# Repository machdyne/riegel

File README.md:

# Riegel Computer

Riegel is an FPGA computer designed by Lone Dynamics Corporation.

This repo contains schematics, PCB layouts, pinouts, a 3D-printable case, example gateware and documentation.

Find more information on the [Riegel product page](https://machdyne.com/product/riegel-computer/).

## Blinky 

Building the blinky example requires [Yosys](https://github.com/YosysHQ/yosys), [nextpnr-ice40](https://github.com/YosysHQ/nextpnr) and [IceStorm](https://github.com/YosysHQ/icestorm).

Assuming they are installed, you can simply type `make` to build the gateware, which will be written to output/blinky.bin. You can then use [ldprog](https://github.com/machdyne/ldprog) to write the gateware to the device.

## Zucker

[Zucker](https://github.com/machdyne/zucker) is a RISC-V SOC designed specifically for Riegel hardware.

## USB Bootloader

Riegel supports updating the flash MMOD over its USB-C port with the USB DFU (Device Firmware Upgrade) protocol. When Riegel powers on (or restarts) the USB bootloader waits 5 seconds for a USB command and then continues the boot process, if it receives a command it will wait until the device is detached (with `dfu-util -e`) or rebooted (with `ldprog -r`).

In order to install the USB bootloader you will need to use the ISP header and [ldprog](https://github.com/machdyne/ldprog). Make sure you have first installed the software required to build the Blinky example above.

```
git clone https://github.com/machdyne/tinydfu-bootloader
cd tinydfu-bootloader/boards/riegel
make
make prog
```

Now you can program the flash MMOD over USB:

```
ldprog -r
sudo dfu-util -a 0 -D zucker/output/soc.bin
sudo dfu-util -a 1 -D zucker/apps/lix/lix.bin
```

Note: It may be necessary to remove the MicroSD card before programming with DFU.

Exit the bootloader and continue booting:

```
sudo dfu-util -e -a 0
```

## ISP Header

The ISP header can be used to program the FPGA SRAM as well as the MMOD flash memory. 

```
1 2
3 4
5 6
7 8
```

| Pin | Signal |
| --- | ------ |
| 1 | CSPI\_SS |
| 2 | CSPI\_SCK |
| 3 | CSPI\_SI |
| 4 | CSPI\_SO |
| 5 | CRESET |
| 6 | CDONE |
| 7 | GND |
| 8 | PWR3V3 (out) |

## Board Revisions

| Revision | Notes |
| -------- | ----- |
| V3B | Latest production board |
| V4 | Work in progress; improves USB routing  |

## License

The contents of this repo are released under the [Lone Dynamics Open License](LICENSE.md) with the following exceptions:

- The KiCad design files contain parts of the [kicad-pmod](https://github.com/mithro/kicad-pmod) library which is released under the [Apache License, Version 2.0](https://www.apache.org/licenses/LICENSE-2.0.html).

- The KiCad design files may contain symbols and footprints released under other licenses; please contact us if we've failed to give proper attribution.

Note: You can use these designs for commercial purposes but we ask that instead of producing exact clones, that you either replace our trademarks and logos with your own or add your own next to ours.

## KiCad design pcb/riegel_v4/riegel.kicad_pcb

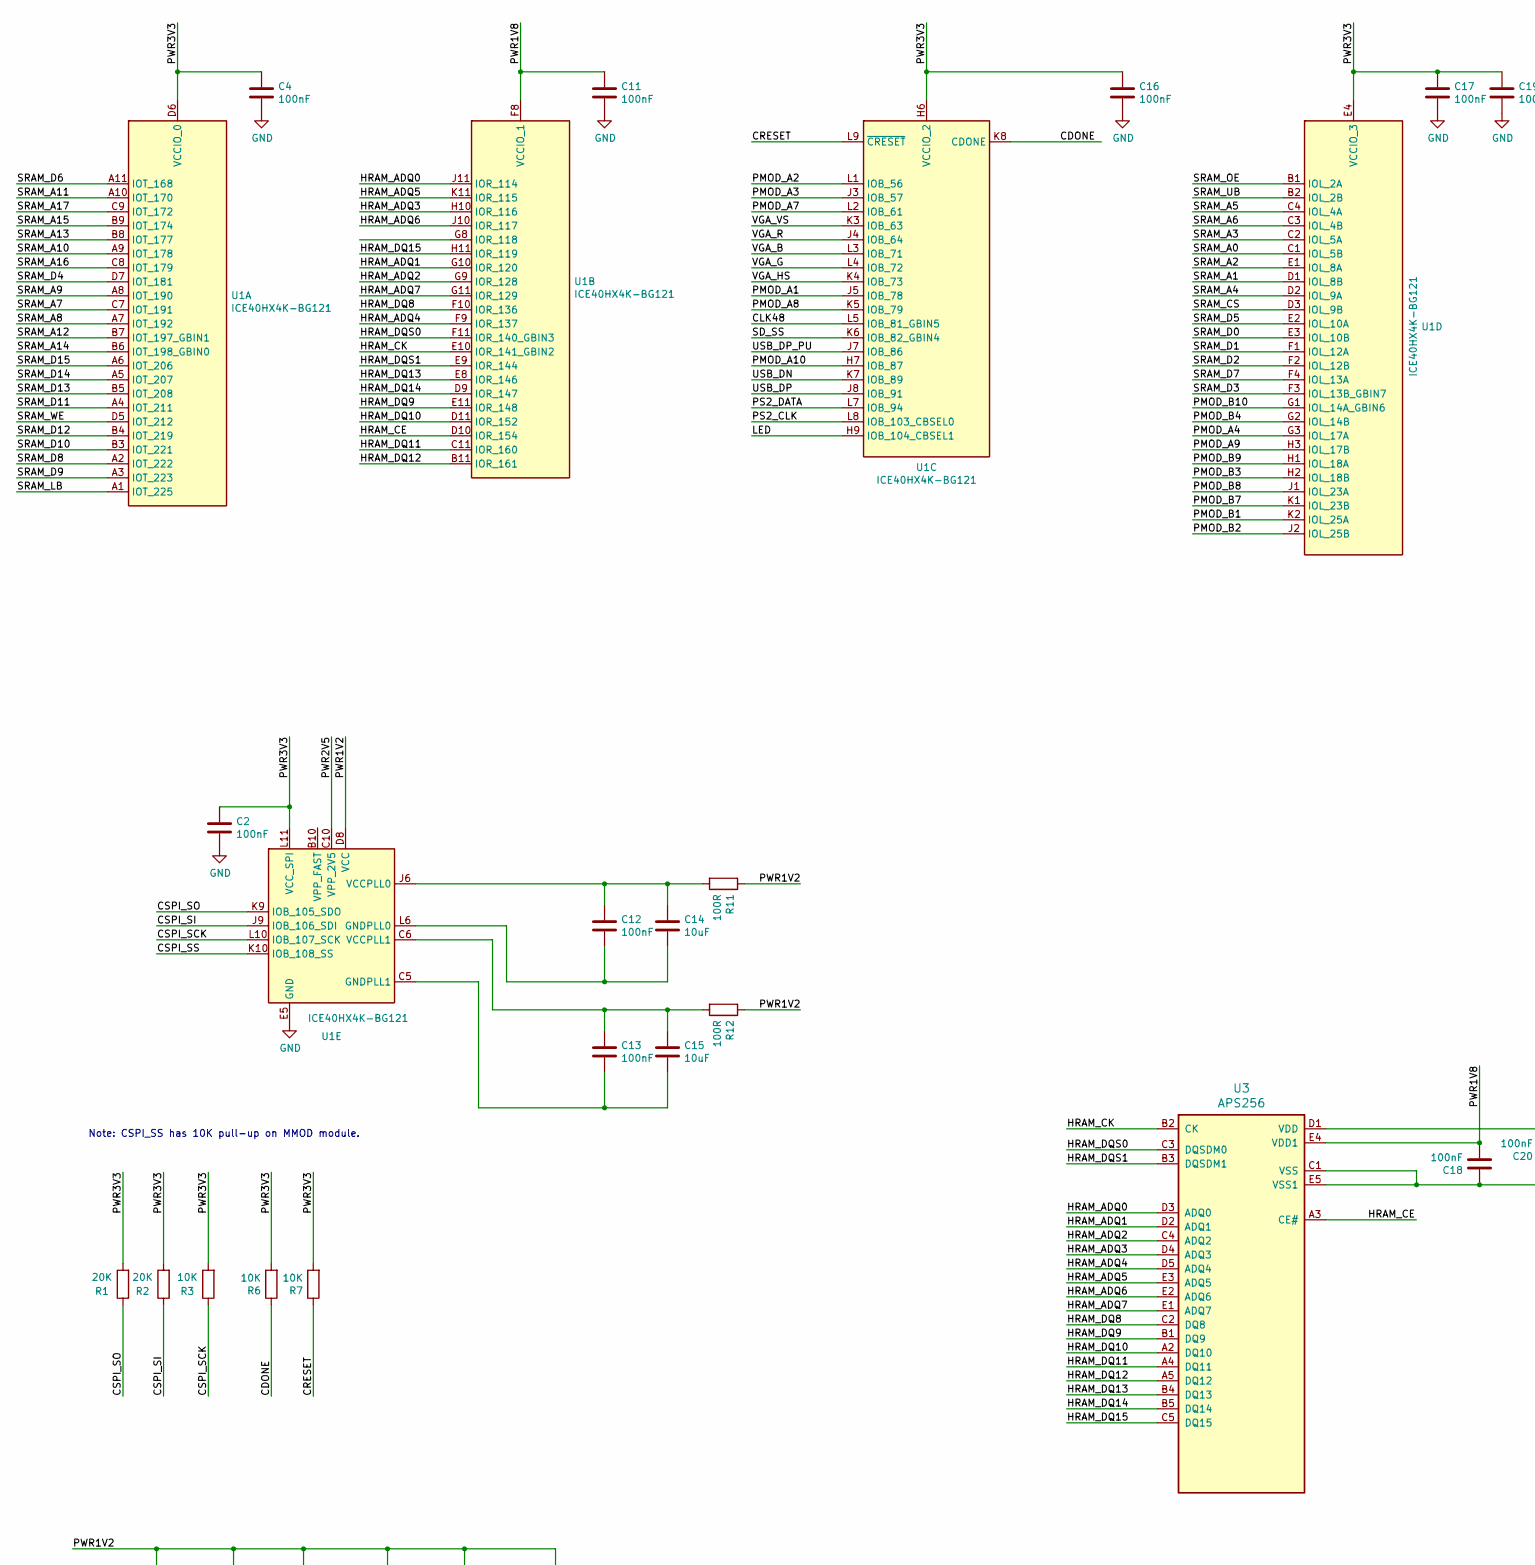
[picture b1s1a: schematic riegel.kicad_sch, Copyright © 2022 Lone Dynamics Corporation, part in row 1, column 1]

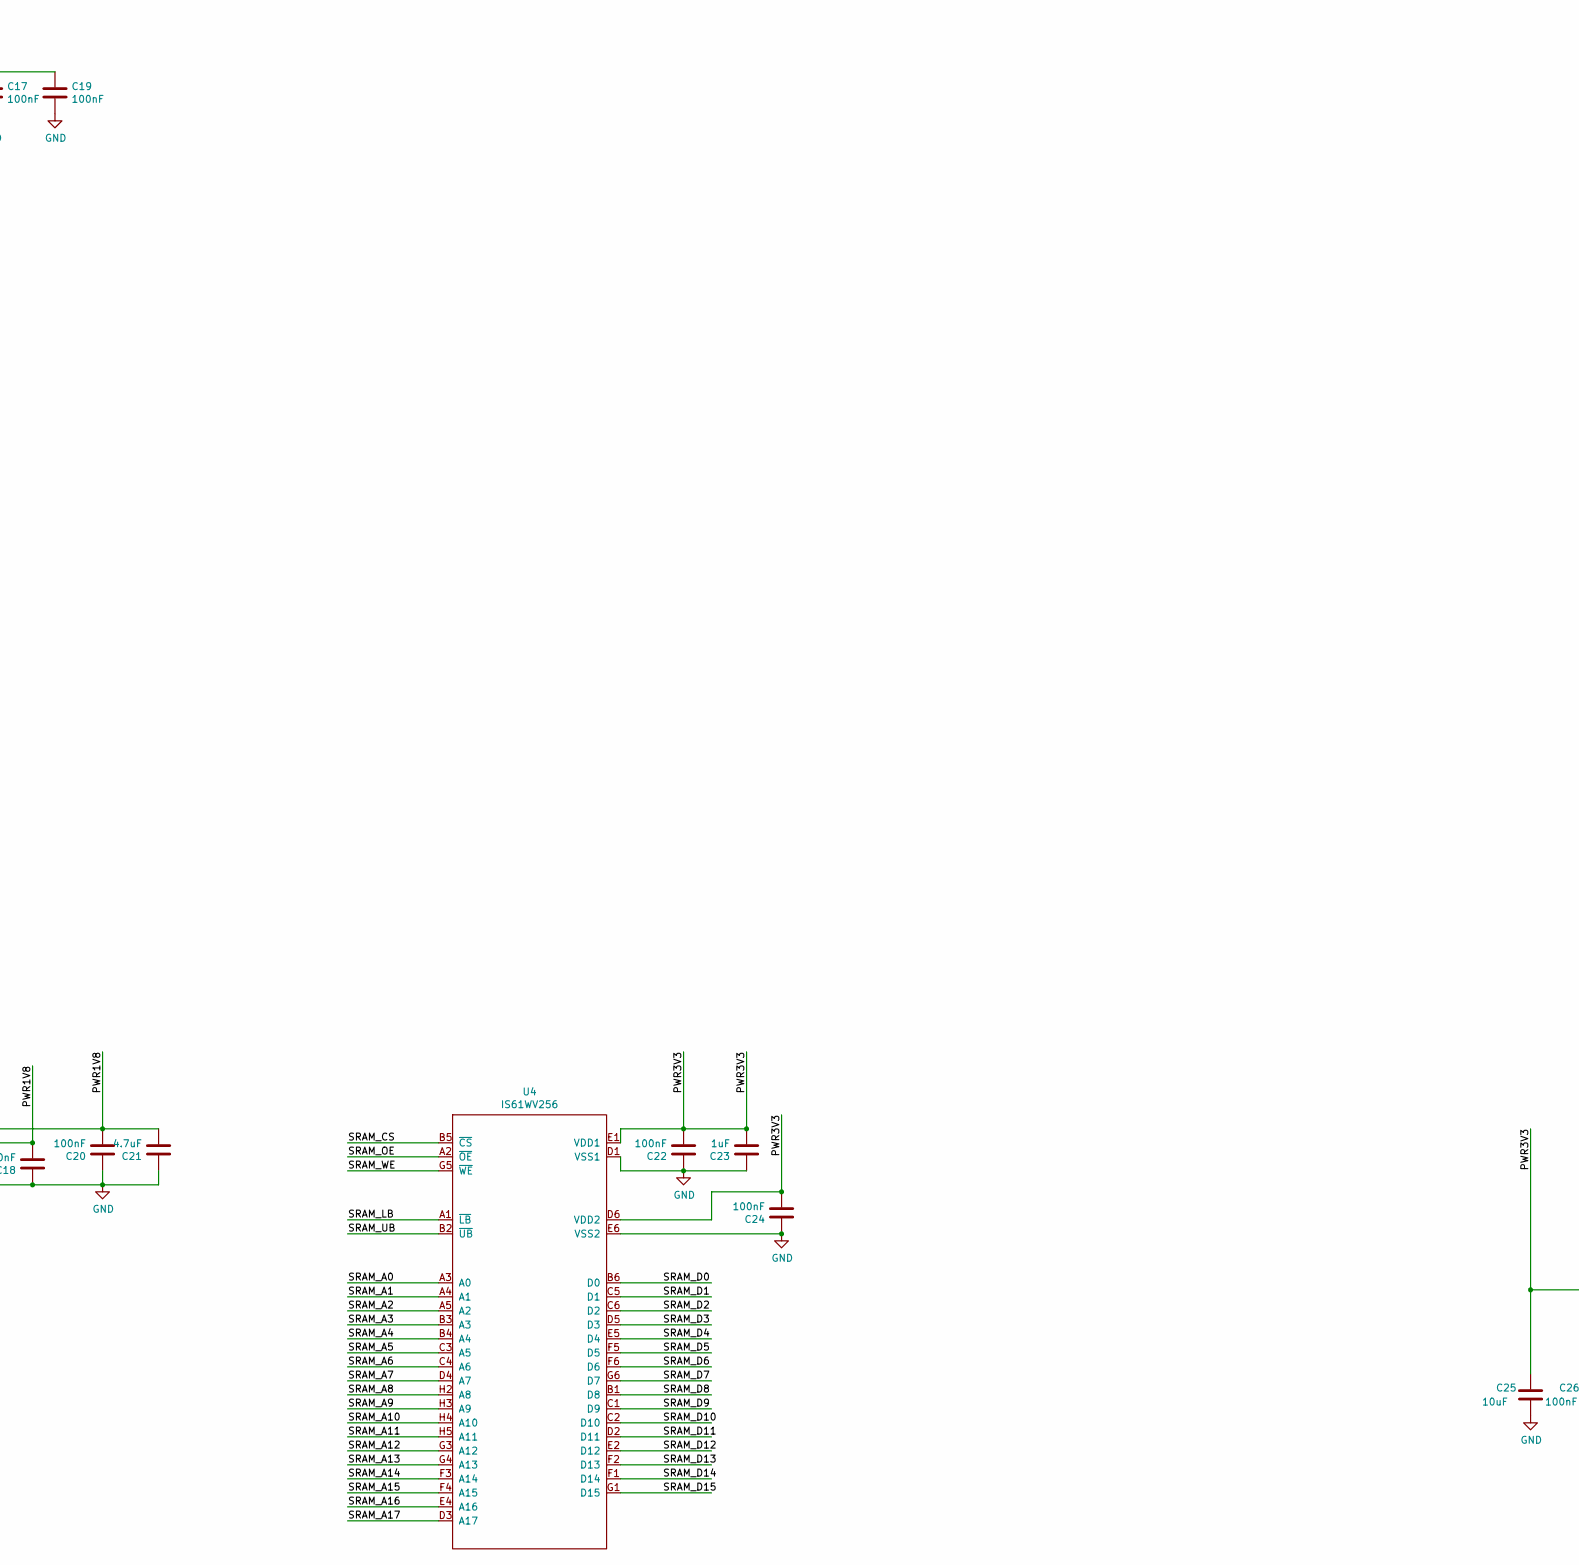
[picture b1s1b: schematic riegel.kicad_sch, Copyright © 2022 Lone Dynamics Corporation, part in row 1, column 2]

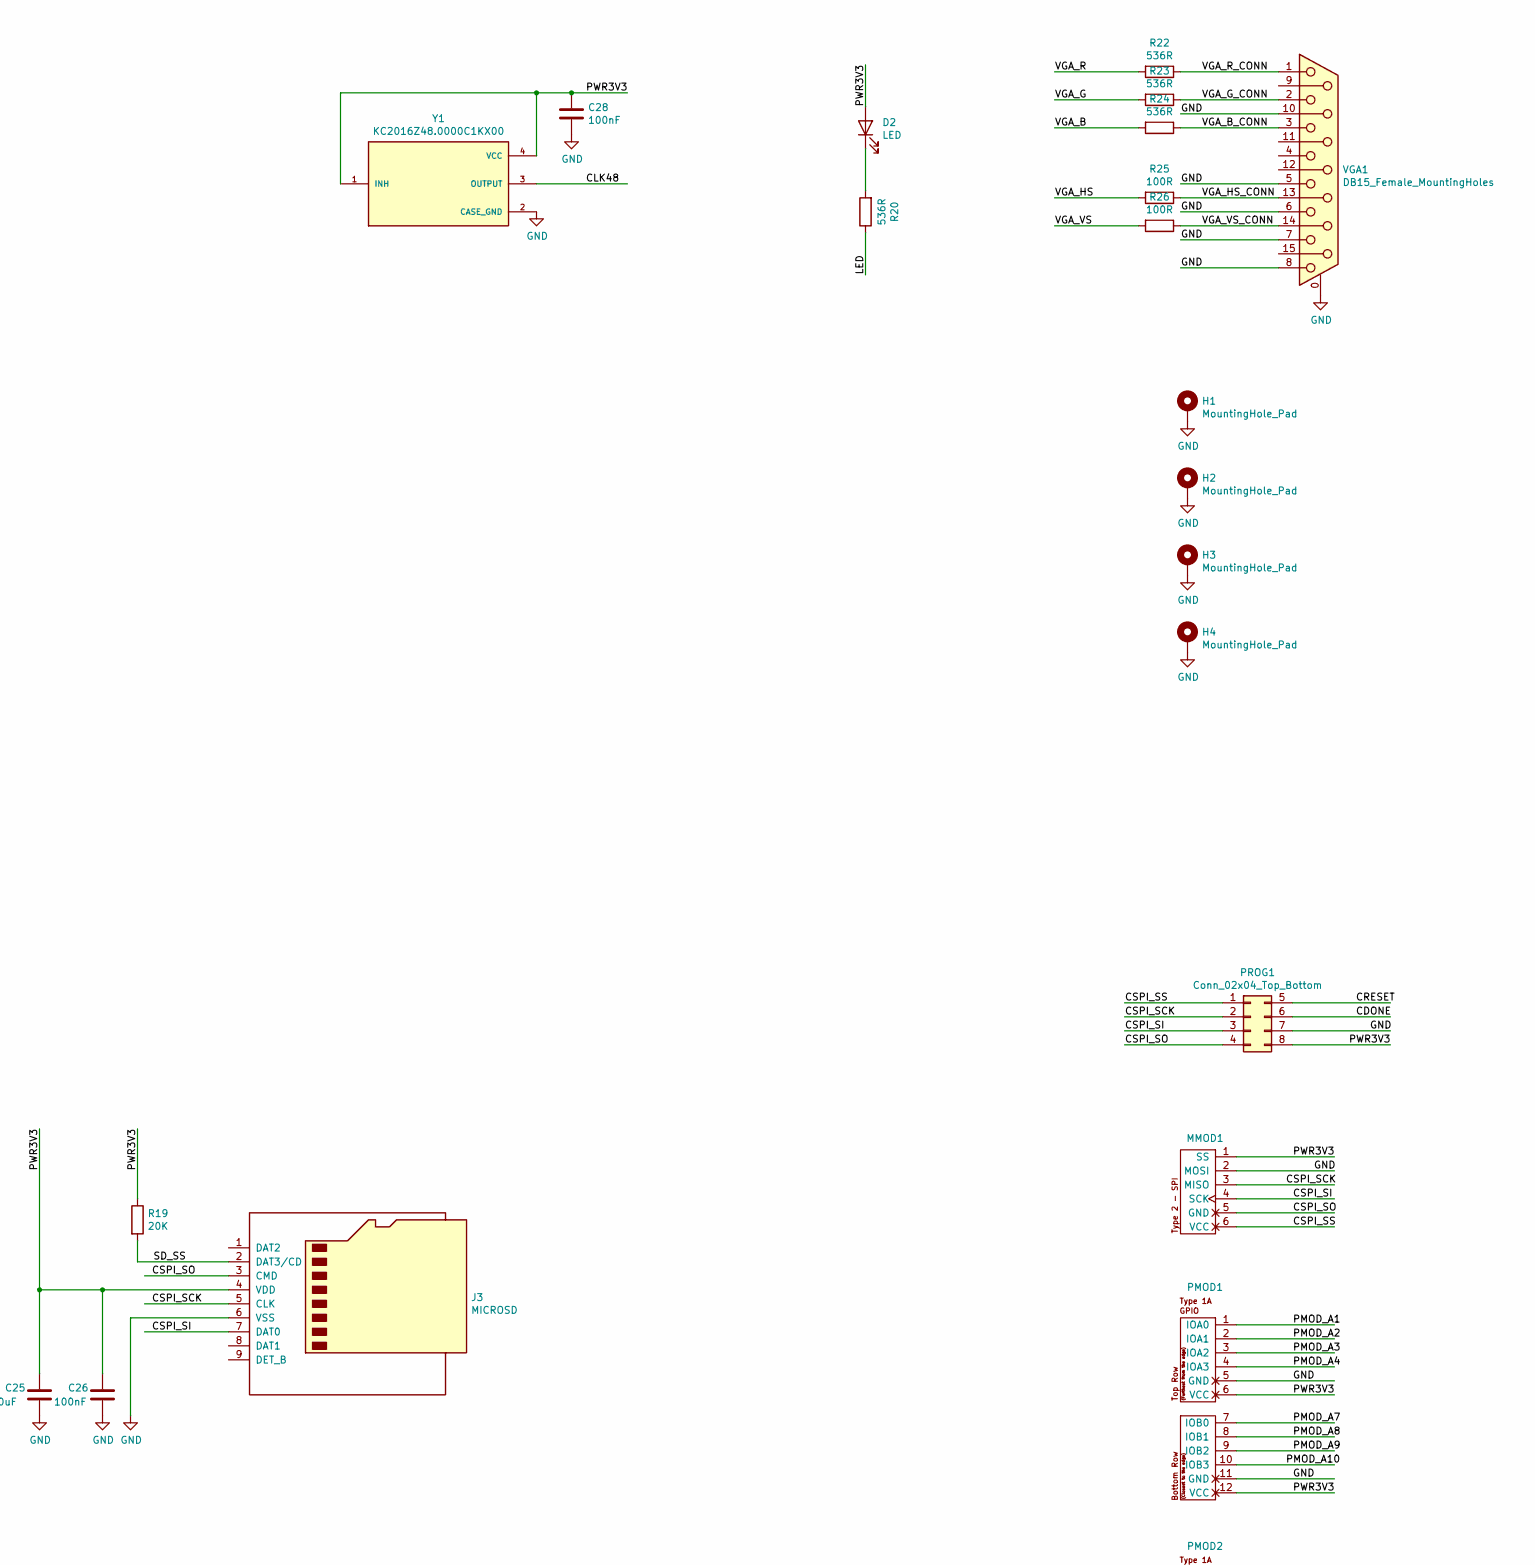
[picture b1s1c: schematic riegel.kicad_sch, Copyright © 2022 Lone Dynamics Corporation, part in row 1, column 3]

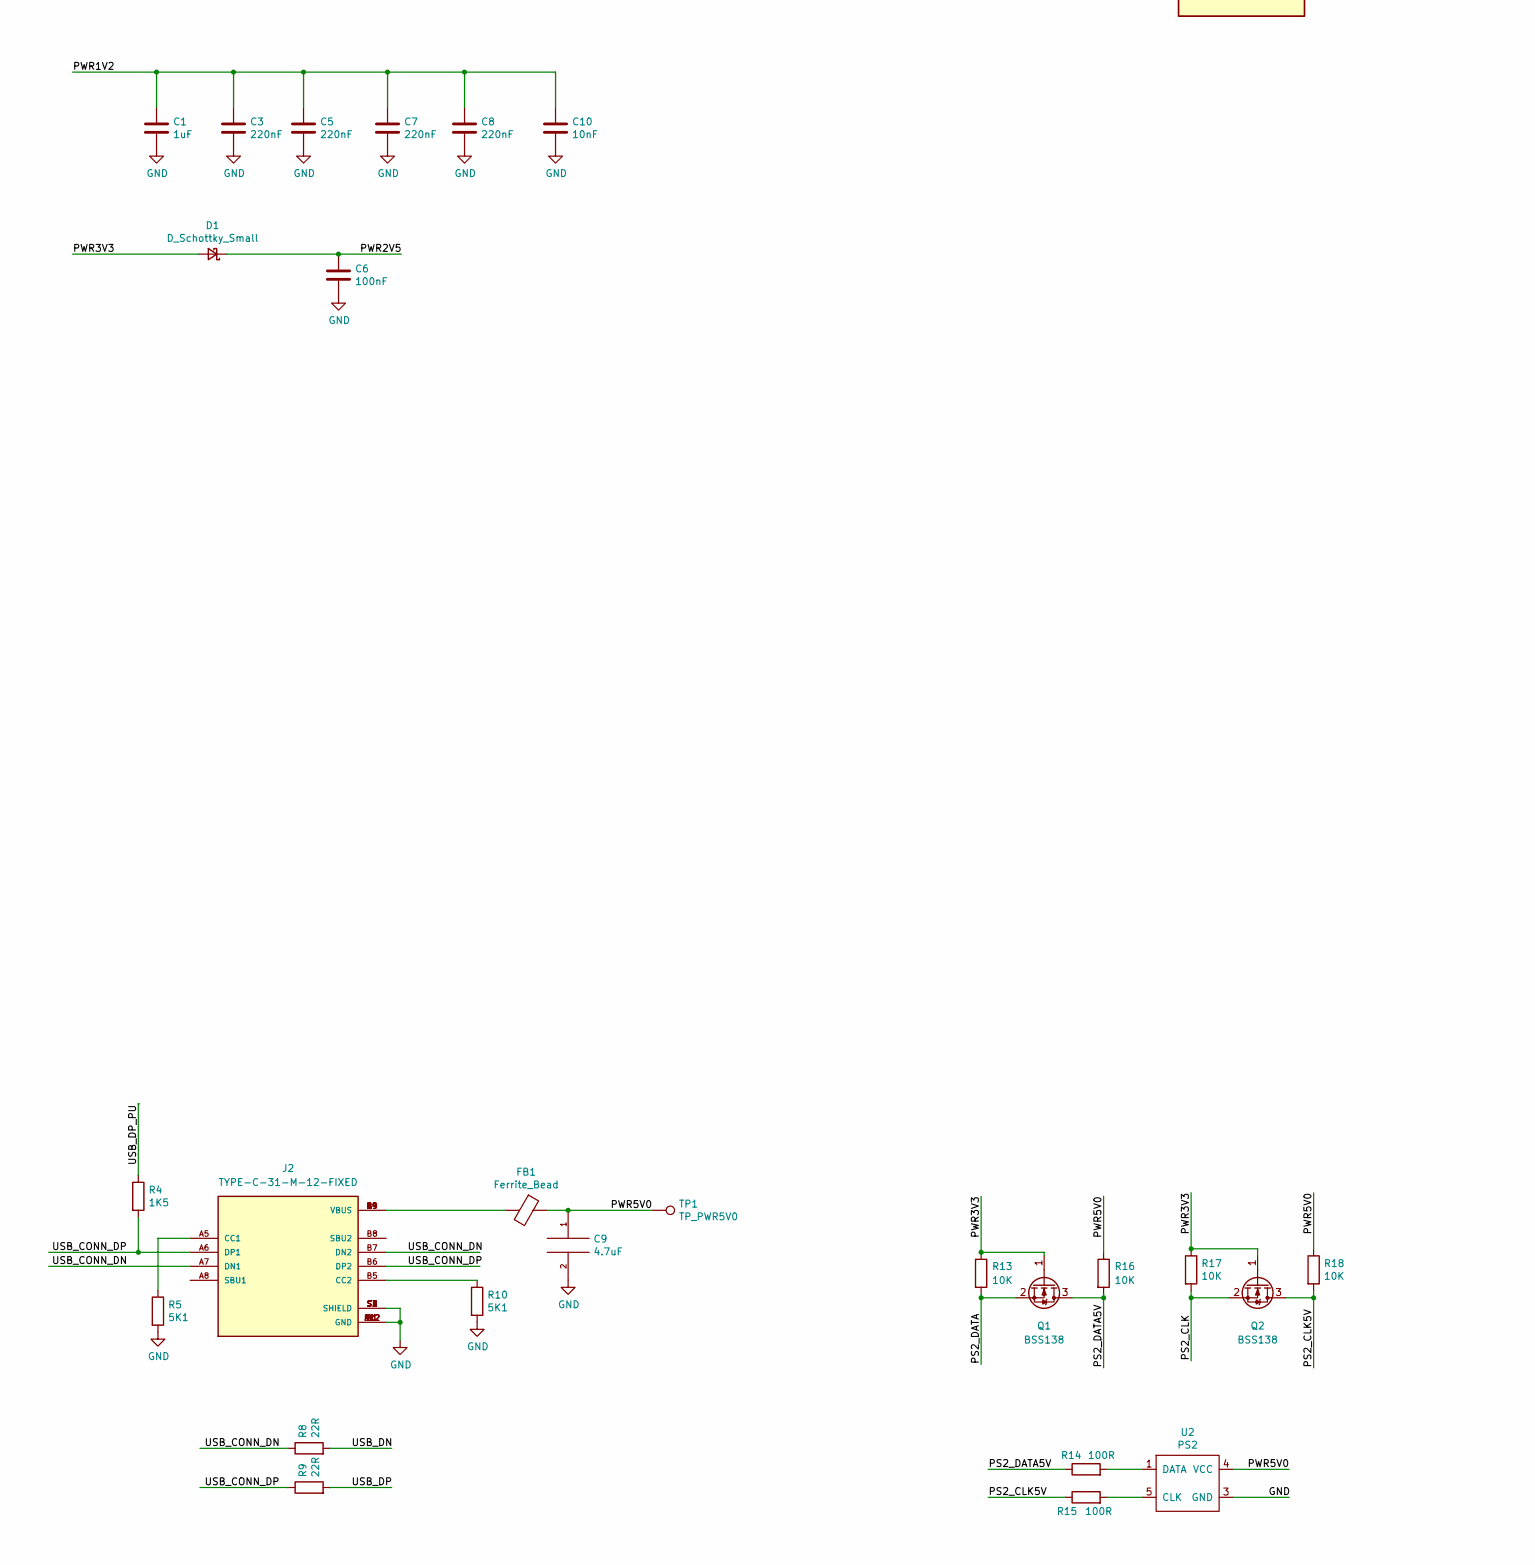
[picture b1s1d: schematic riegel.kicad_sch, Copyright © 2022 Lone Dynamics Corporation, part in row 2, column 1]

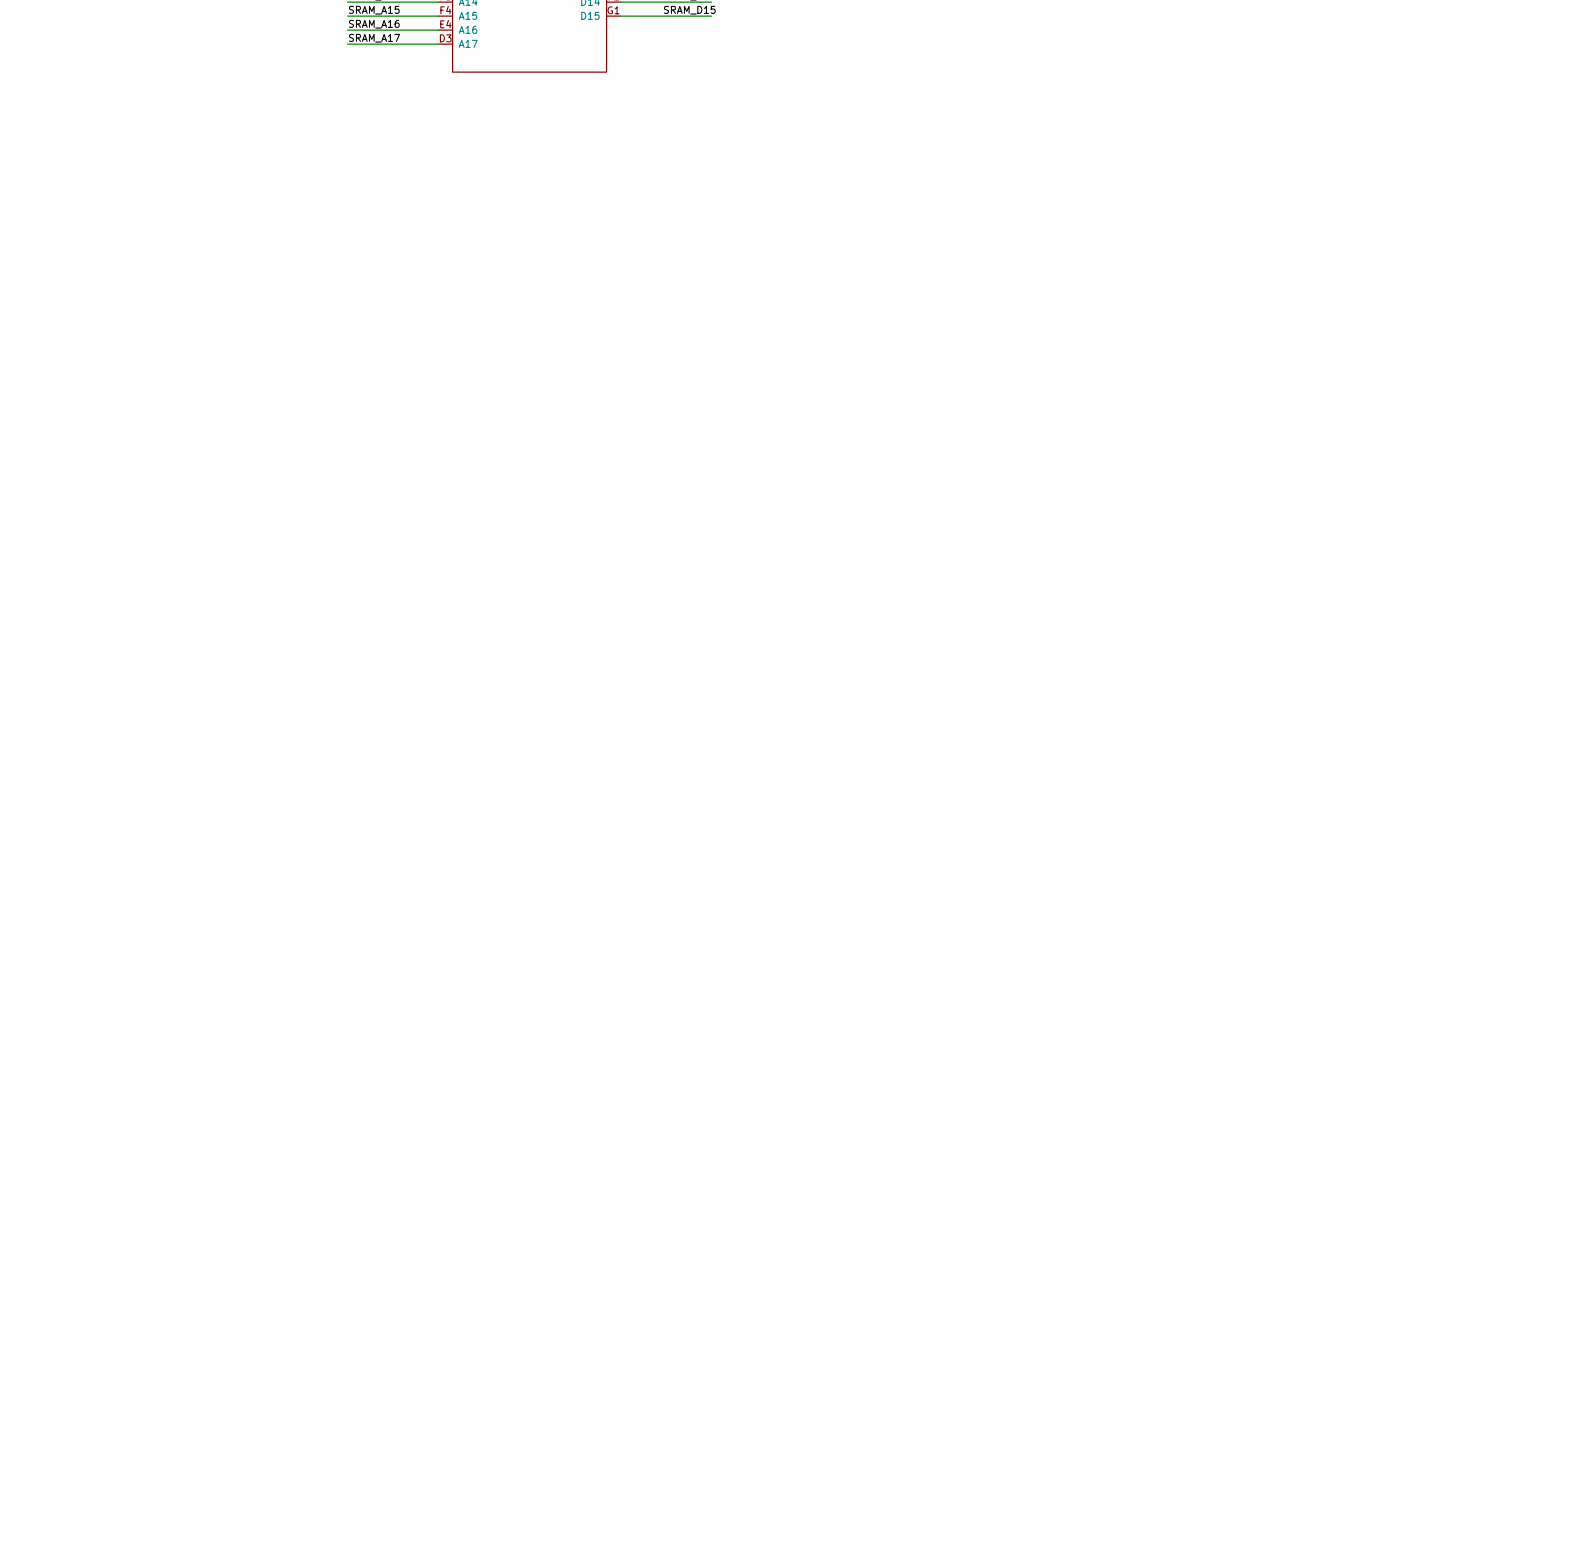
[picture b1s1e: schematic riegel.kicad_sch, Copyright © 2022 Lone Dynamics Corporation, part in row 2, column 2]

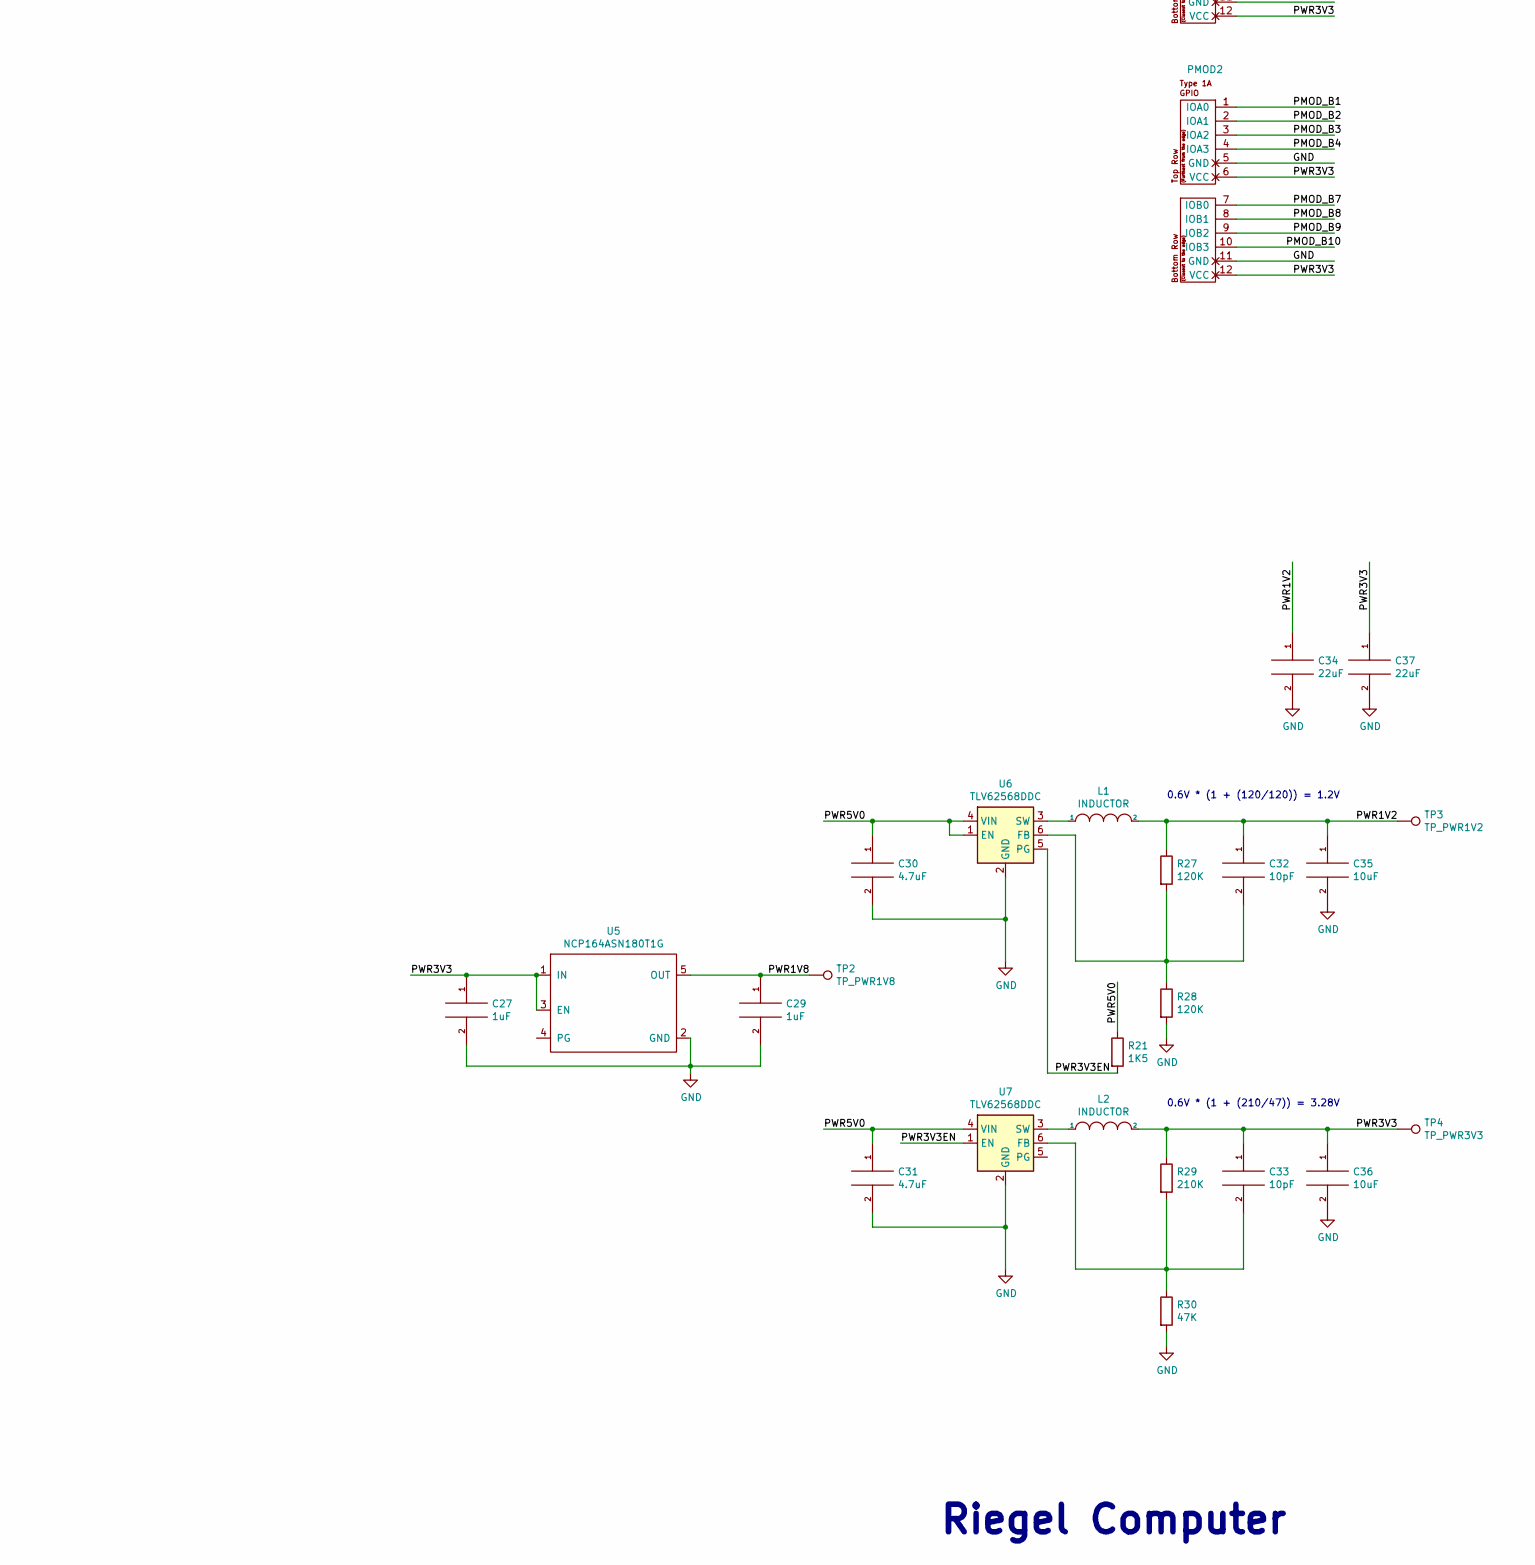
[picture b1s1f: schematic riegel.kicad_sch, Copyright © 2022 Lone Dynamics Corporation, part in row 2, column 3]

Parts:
C1, C27, C29: 1uF; C_0603_1608Metric
C2, C4, C6, C11, C12, C13, C16, C17, C19: 100nF; C_0603_1608Metric
C3, C5, C7, C8: 220nF; C_0603_1608Metric
C9, C21: 4.7uF; R_0603_1608Metric
C10: 10nF; C_0603_1608Metric
C14, C15, C35, C36: 10uF; C_0603_1608Metric
C18, C20, C22, C24, C26, C28: 100nF; R_0603_1608Metric
C23: 1uF; R_0603_1608Metric
C25: 10uF; R_0603_1608Metric
C30, C31: 4.7uF; C_0603_1608Metric
C32, C33: 10pF; C_0603_1608Metric
C34, C37: 22uF; C_0603_1608Metric
D1: D_Schottky_Small; D_0603_1608Metric
D2: LED; LED_0603_1608Metric
FB1: Ferrite_Bead; R_0603_1608Metric
H1, H2, H3, H4: MountingHole_Pad; MountingHole_3.2mm_M3_Pad
J2: TYPE-C-31-M-12-FIXED; USB_C_Receptacle_HRO_TYPE-C-31-M-12; PARTREV A
J3: MICROSD; SDCARD
L1, L2: INDUCTOR; L_0805_2012Metric
MMOD1: PMOD-Device-x1-Type-2-SPI; PinSocket_1x06_P2.54mm_Horizontal
PMOD1, PMOD2: PMOD-Device-x2-Type-1A-GPIO; PMOD_2x06_HOST
PROG1: Conn_02x04_Top_Bottom; PinHeader_2x04_P2.54mm_Vertical
Q1, Q2: BSS138; SOT-323_SC-70
R1, R2, R19: 20K; R_0603_1608Metric
R3, R6, R7, R13, R16, R17, R18: 10K; R_0603_1608Metric
R4, R21: 1K5; R_0603_1608Metric
R5, R10: 5K1; R_0603_1608Metric
R8, R9: 22R; R_0603_1608Metric
R11, R12, R14, R15, R25, R26: 100R; R_0603_1608Metric
R20, R22, R23, R24: 536R; R_0603_1608Metric
R27, R28: 120K; R_0603_1608Metric
R29: 210K; R_0603_1608Metric
R30: 47K; R_0603_1608Metric
TP1: TP_PWR5V0; TestPoint_THTPad_D1.0mm_Drill0.5mm
TP2: TP_PWR1V8; TestPoint_THTPad_D1.0mm_Drill0.5mm
TP3: TP_PWR1V2; TestPoint_THTPad_D1.0mm_Drill0.5mm
TP4: TP_PWR3V3; TestPoint_THTPad_D1.0mm_Drill0.5mm
U1: ICE40HX4K-BG121; BGA-121_9.0x9.0mm_Layout11x11_P0.8mm_Ball0.4mm_Pad0.35mm_NS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
U2: PS2; MINI-DIN-6-FULL-SHIELD
U3: APS256; APS256_BGA_24
U4: IS61WV256; BGA48C75P8X6_800X600X120N
U5: NCP164ASN180T1G; TSOP-5_1.65x3.05mm_P0.95mm
U6, U7: TLV62568DDC; SOT-23-6
VGA1: DB15_Female_MountingHoles; DSUB-15-HD_Female_Horizontal_P2.29x1.98mm_EdgePinOffset3.03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
Y1: KC2016Z48.0000C1KX00; OSC_KC2016Z13.5600C1KX00; PARTREV November 2020

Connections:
/CDONE: PROG1.6, R6.1, U1.K8 (CDONE)
/CLK48: U1.L5 (IOB_81_GBIN5), Y1.3 (OUTPUT)
/CRESET: PROG1.5, R7.1, U1.L9 (~CRESET)
/CSPI_SCK: J3.5 (CLK), MMOD1.3 (MISO), PROG1.2, R3.1, U1.L10 (IOB_107_SCK)
/CSPI_SI: J3.7 (DAT0), MMOD1.4 (SCK), PROG1.3, R2.1, U1.J9 (IOB_106_SDI)
/CSPI_SO: J3.3 (CMD), MMOD1.5 (GND), PROG1.4, R1.1, U1.K9 (IOB_105_SDO)
/CSPI_SS: MMOD1.6 (VCC), PROG1.1, U1.K10 (IOB_108_SS)
/HRAM_ADQ0: U1.J11 (IOR_114), U3.D3 (ADQ0)
/HRAM_ADQ1: U1.G10 (IOR_120), U3.D2 (ADQ1)
/HRAM_ADQ2: U1.G9 (IOR_128), U3.C4 (ADQ2)
/HRAM_ADQ3: U1.H10 (IOR_116), U3.D4 (ADQ3)
/HRAM_ADQ4: U1.F9 (IOR_137), U3.D5 (ADQ4)
/HRAM_ADQ5: U1.K11 (IOR_115), U3.E3 (ADQ5)
/HRAM_ADQ6: U1.J10 (IOR_117), U3.E2 (ADQ6)
/HRAM_ADQ7: U1.G11 (IOR_129), U3.E1 (ADQ7)
/HRAM_CE: U1.D10 (IOR_154), U3.A3 (CE#)
/HRAM_CK: U1.E10 (IOR_141_GBIN2), U3.B2 (CK)
/HRAM_DQ8: U1.F10 (IOR_136), U3.C2 (DQ8)
/HRAM_DQ9: U1.E11 (IOR_148), U3.B1 (DQ9)
/HRAM_DQ10: U1.D11 (IOR_152), U3.A2 (DQ10)
/HRAM_DQ11: U1.C11 (IOR_160), U3.A4 (DQ11)
/HRAM_DQ12: U1.B11 (IOR_161), U3.A5 (DQ12)
/HRAM_DQ13: U1.E8 (IOR_146), U3.B4 (DQ13)
/HRAM_DQ14: U1.D9 (IOR_147), U3.B5 (DQ14)
/HRAM_DQ15: U1.H11 (IOR_119), U3.C5 (DQ15)
/HRAM_DQS0: U1.F11 (IOR_140_GBIN3), U3.C3 (DQSDM0)
/HRAM_DQS1: U1.E9 (IOR_144), U3.B3 (DQSDM1)
/LED: R20.1, U1.H9 (IOB_104_CBSEL1)
/PMOD_A1: PMOD1.1 (IOA0), U1.J5 (IOB_78)
/PMOD_A2: PMOD1.2 (IOA1), U1.L1 (IOB_56)
/PMOD_A3: PMOD1.3 (IOA2), U1.J3 (IOB_57)
/PMOD_A4: PMOD1.4 (IOA3), U1.G3 (IOL_17A)
/PMOD_A7: PMOD1.7 (IOB0), U1.L2 (IOB_61)
/PMOD_A8: PMOD1.8 (IOB1), U1.K5 (IOB_79)
/PMOD_A9: PMOD1.9 (IOB2), U1.H3 (IOL_17B)
/PMOD_A10: PMOD1.10 (IOB3), U1.H7 (IOB_87)
/PMOD_B1: PMOD2.1 (IOA0), U1.K2 (IOL_25A)
/PMOD_B2: PMOD2.2 (IOA1), U1.J2 (IOL_25B)
/PMOD_B3: PMOD2.3 (IOA2), U1.H2 (IOL_18B)
/PMOD_B4: PMOD2.4 (IOA3), U1.G2 (IOL_14B)
/PMOD_B7: PMOD2.7 (IOB0), U1.K1 (IOL_23B)
/PMOD_B8: PMOD2.8 (IOB1), U1.J1 (IOL_23A)
/PMOD_B9: PMOD2.9 (IOB2), U1.H1 (IOL_18A)
/PMOD_B10: PMOD2.10 (IOB3), U1.G1 (IOL_14A_GBIN6)
/PS2_CLK: Q2.2 (S), R17.2, U1.L8 (IOB_103_CBSEL0)
/PS2_CLK5V: Q2.3 (D), R15.1, R18.2
/PS2_DATA: Q1.2 (S), R13.2, U1.L7 (IOB_94)
/PS2_DATA5V: Q1.3 (D), R14.1, R16.2
/PWR1V2: C1.1, C3.1, C5.1, C7.1, C8.1, C10.1, C32.1, C34.1, C35.1, L1.2, R11.1, R12.1, R27.1, TP3.1, U1.D4 (VCC), U1.D8 (VCC), U1.H4 (VCC), U1.H8 (VCC)
/PWR1V8: C11.1, C18.2, C20.2, C21.2, C29.1, TP2.1, U1.F8 (VCCIO_1), U3.D1 (VDD), U3.E4 (VDD1), U5.5 (OUT)
/PWR2V5: C6.1, D1.1 (K), U1.C10 (VPP_2V5)
/PWR3V3: C2.1, C4.1, C16.1, C17.1, C19.1, C22.2, C23.2, C24.2, C25.1, C26.1, C27.1, C28.1, C33.1, C36.1, C37.1, D1.2 (A), D2.2 (A), J3.4 (VDD), L2.2, MMOD1.1 (SS), PMOD1.6 (VCC), PMOD1.12 (VCC), PMOD2.6 (VCC), PMOD2.12 (VCC), PROG1.8, Q1.1 (G), Q2.1 (G), R1.2, R2.2, R3.2, R6.2, R7.2, R13.1, R17.1, R19.1, R29.1, TP4.1, U1.D6 (VCCIO_0), U1.E4 (VCCIO_3), U1.G4 (VCCIO_3), U1.H6 (VCCIO_2), U1.L11 (VCC_SPI), U4.D6 (VDD2), U4.E1 (VDD1), U5.1 (IN), U5.3 (EN), Y1.1 (INH), Y1.4 (VCC)
/PWR3V3EN: R21.2, U6.5 (PG), U7.1 (EN)
/PWR5V0: C9.1, C30.1, C31.1, FB1.1, R16.1, R18.1, R21.1, TP1.1, U2.4 (VCC), U6.1 (EN), U6.4 (VIN), U7.4 (VIN)
/SD_SS: J3.2 (DAT3/CD), R19.2, U1.K6 (IOB_82_GBIN4)
/SRAM_A0: U1.C1 (IOL_5B), U4.A3 (A0)
/SRAM_A1: U1.D1 (IOL_8B), U4.A4 (A1)
/SRAM_A2: U1.E1 (IOL_8A), U4.A5 (A2)
/SRAM_A3: U1.C2 (IOL_5A), U4.B3 (A3)
/SRAM_A4: U1.D2 (IOL_9A), U4.B4 (A4)
/SRAM_A5: U1.C4 (IOL_4A), U4.C3 (A5)
/SRAM_A6: U1.C3 (IOL_4B), U4.C4 (A6)
/SRAM_A7: U1.C7 (IOT_191), U4.D4 (A7)
/SRAM_A8: U1.A7 (IOT_192), U4.H2 (A8)
/SRAM_A9: U1.A8 (IOT_190), U4.H3 (A9)
/SRAM_A10: U1.A9 (IOT_178), U4.H4 (A10)
/SRAM_A11: U1.A10 (IOT_170), U4.H5 (A11)
/SRAM_A12: U1.B7 (IOT_197_GBIN1), U4.G3 (A12)
/SRAM_A13: U1.B8 (IOT_177), U4.G4 (A13)
/SRAM_A14: U1.B6 (IOT_198_GBIN0), U4.F3 (A14)
/SRAM_A15: U1.B9 (IOT_174), U4.F4 (A15)
/SRAM_A16: U1.C8 (IOT_179), U4.E4 (A16)
/SRAM_A17: U1.C9 (IOT_172), U4.D3 (A17)
/SRAM_CS: U1.D3 (IOL_9B), U4.B5 (~CS)
/SRAM_D0: U1.E3 (IOL_10B), U4.B6 (D0)
/SRAM_D1: U1.F1 (IOL_12A), U4.C5 (D1)
/SRAM_D2: U1.F2 (IOL_12B), U4.C6 (D2)
/SRAM_D3: U1.F3 (IOL_13B_GBIN7), U4.D5 (D3)
/SRAM_D4: U1.D7 (IOT_181), U4.E5 (D4)
/SRAM_D5: U1.E2 (IOL_10A), U4.F5 (D5)
/SRAM_D6: U1.A11 (IOT_168), U4.F6 (D6)
/SRAM_D7: U1.F4 (IOL_13A), U4.G6 (D7)
/SRAM_D8: U1.A2 (IOT_222), U4.B1 (D8)
/SRAM_D9: U1.A3 (IOT_223), U4.C1 (D9)
/SRAM_D10: U1.B3 (IOT_221), U4.C2 (D10)
/SRAM_D11: U1.A4 (IOT_211), U4.D2 (D11)
/SRAM_D12: U1.B4 (IOT_219), U4.E2 (D12)
/SRAM_D13: U1.B5 (IOT_208), U4.F2 (D13)
/SRAM_D14: U1.A5 (IOT_207), U4.F1 (D14)
/SRAM_D15: U1.A6 (IOT_206), U4.G1 (D15)
/SRAM_LB: U1.A1 (IOT_225), U4.A1 (~LB)
/SRAM_OE: U1.B1 (IOL_2A), U4.A2 (~OE)
/SRAM_UB: U1.B2 (IOL_2B), U4.B2 (~UB)
/SRAM_WE: U1.D5 (IOT_212), U4.G5 (~WE)
/USB_CONN_DN: J2.A7 (DN1), J2.B7 (DN2), R8.1
/USB_CONN_DP: J2.A6 (DP1), J2.B6 (DP2), R4.2, R9.1
/USB_DN: R8.2, U1.K7 (IOB_89)
/USB_DP: R9.2, U1.J8 (IOB_91)
/USB_DP_PU: R4.1, U1.J7 (IOB_86)
/VGA_B: R24.2, U1.L3 (IOB_71)
/VGA_B_CONN: R24.1, VGA1.3
/VGA_G: R23.2, U1.L4 (IOB_72)
/VGA_G_CONN: R23.1, VGA1.2
/VGA_HS: R25.2, U1.K4 (IOB_73)
/VGA_HS_CONN: R25.1, VGA1.13
/VGA_R: R22.2, U1.J4 (IOB_64)
/VGA_R_CONN: R22.1, VGA1.1
/VGA_VS: R26.2, U1.K3 (IOB_63)
/VGA_VS_CONN: R26.1, VGA1.14
GND: C1.2, C2.2, C3.2, C4.2, C5.2, C6.2, C7.2, C8.2, C9.2, C10.2, C11.2, C16.2, C17.2, C18.1, C19.2, C20.1, C21.1, C22.1, C23.1, C24.1, C25.2, C26.2, C27.2, C28.2, C29.2, C30.2, C31.2, C34.2, C35.2, C36.2, C37.2, H1.1, H2.1, H3.1, H4.1, J2.A1 (GND), J2.A12 (GND), J2.B1 (GND), J2.B12 (GND), J2.S1 (SHIELD), J2.S2 (SHIELD), J2.S3 (SHIELD), J2.S4 (SHIELD), J3.6 (VSS), MMOD1.2 (MOSI), PMOD1.5 (GND), PMOD1.11 (GND), PMOD2.5 (GND), PMOD2.11 (GND), PROG1.7, R5.2, R10.2, R28.2, R30.2, U1.E5 (GND), U1.E6 (GND), U1.E7 (GND), U1.F5 (GND), U1.F6 (GND), U1.F7 (GND), U1.G5 (GND), U1.G6 (GND), U1.G7 (GND), U1.H5 (GND), U2.3 (GND), U3.C1 (VSS), U3.E5 (VSS1), U4.D1 (VSS1), U4.E6 (VSS2), U5.2 (GND), U6.2 (GND), U7.2 (GND), VGA1.0 (PAD), VGA1.5, VGA1.6, VGA1.7, VGA1.8, VGA1.10, Y1.2 (CASE_GND)
unnamed: C12.1, C14.1, R11.2, U1.J6 (VCCPLL0)
unnamed: C12.2, C14.2, U1.L6 (GNDPLL0)
unnamed: C13.1, C15.1, R12.2, U1.C6 (VCCPLL1)
unnamed: C13.2, C15.2, U1.C5 (GNDPLL1)
unnamed: C32.2, R27.2, R28.1, U6.6 (FB)
unnamed: C33.2, R29.2, R30.1, U7.6 (FB)
unnamed: D2.1 (K), R20.2
unnamed: FB1.2, J2.A4 (VBUS), J2.A9 (VBUS), J2.B4 (VBUS), J2.B9 (VBUS)
unnamed: J2.A5 (CC1), R5.1
unnamed: J2.B5 (CC2), R10.1
unnamed: L1.1, U6.3 (SW)
unnamed: L2.1, U7.3 (SW)
unnamed: R14.2, U2.1 (DATA)
unnamed: R15.2, U2.5 (CLK)

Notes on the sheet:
0.6V * (1 + (120/120)) = 1.2V
0.6V * (1 + (210/47)) = 3.28V
Note: CSPI_SS has 10K pull-up on MMOD module.
Riegel Computer

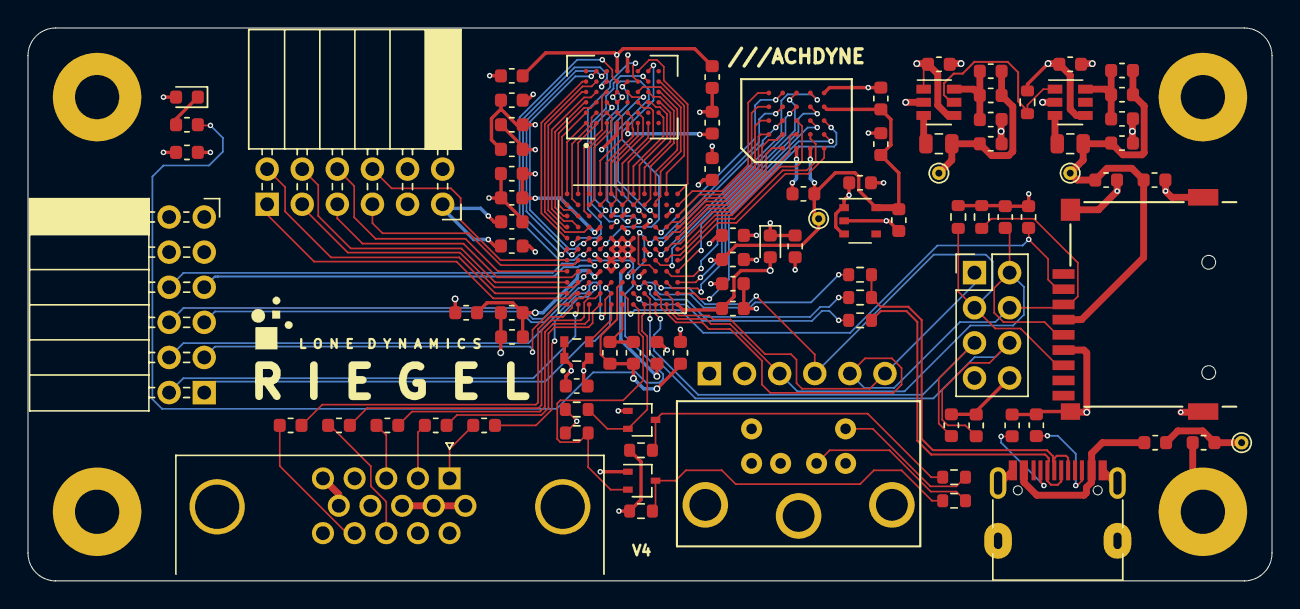
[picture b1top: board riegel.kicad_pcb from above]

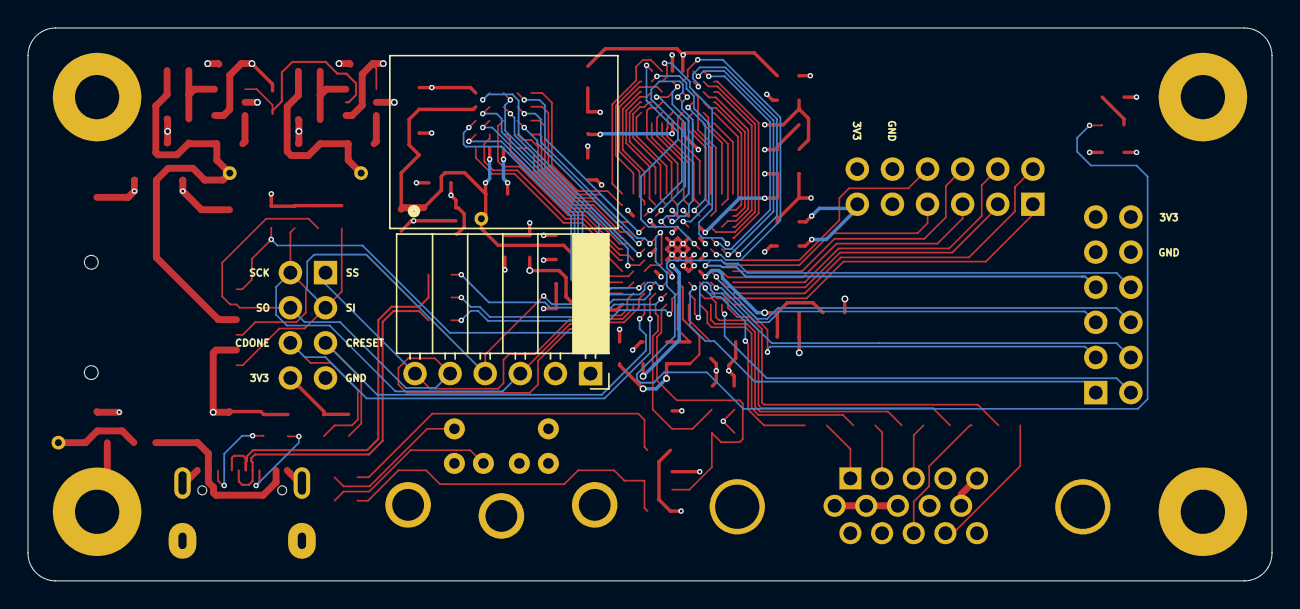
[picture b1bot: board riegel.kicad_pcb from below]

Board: 4 copper layers, 90.0 x 40.0 mm, 98 parts (2 on the bottom side), 124 nets.

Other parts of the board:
CONFIG-MMOD: LD-MMOD

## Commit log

2022-03-14 add image to readme
2022-03-14 add v1 schematics
2022-03-15 update pcfs
2022-03-18 add v3 schematics
2022-03-18 update makefile
2022-03-18 update v3 schematics
2022-03-30 add v3 pcf
2022-04-30 add riegel case
2022-05-18 update image
2022-05-20 update blinky
2023-04-20 add pcb
2023-06-30 improve corner radius
